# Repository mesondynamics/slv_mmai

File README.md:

# Mobile Machine Actuation Interface

**English** · [简体中文](README.zh-CN.md)

A hardware/software interface for retrofitting remote or autonomous control onto
electromechanical and electrohydraulic mobile machines.

MMAI connects an upper-level controller to the steering, propulsion, auxiliaries,
and available state feedback of an existing machine. This repository presents
the engineering approach through schematics, firmware, interface code, and its
development history. Read the source as working design material: it records the
hardware, communication, and actuation choices behind the ECU.

## What it does

- Receives commands from teleoperation or autonomy software.
- Validates commands and manages control authority, timeouts, and output enable.
- Maps commands to electrical interfaces such as relays, CAN-controlled actuators,
  or PWM-driven hydraulic valve coils.
- Acquires machine and actuator state and sends feedback to the upper layer.
- Keeps low-level machine behavior understandable independently of a planner.

The same architecture can be adapted to street sweepers, compactors, agricultural
machines, utility vehicles, and other mobile equipment. The appropriate actuator,
wiring, feedback, and stop behavior depend on the machine. Analog command outputs
or additional serial interfaces are adaptation options, not capabilities implied
for every board in this repository.

## Architecture

The machine-interface ECU sits between the command source and the physical
machine. Steering, propulsion, and auxiliary I/O are separate adaptation paths;
state feedback closes the path through the ECU. Existing manual controls and
machine interlocks are part of that integration.

Upper-level navigation, perception, and route planning are outside the core
actuation boundary. The retained implementation focuses on low-level actuation
and state feedback. See [Architecture](docs/architecture.md)
and [Interfaces](docs/interfaces.md).

## Implementation map

| Area | Start here | What to look for |
| --- | --- | --- |
| H563 actuation ECU | [Hardware project](pcb/roller/ecu/PROJECT1.kicad_pro), [firmware](firmware/roller/ECU/) | Relay switching, proportional-valve current control, CAN steering, protected control boundary |
| Mechanical material | [CAD](cad/), [PCB sources](pcb/) | Physical integration and board development |

Historical directory names are retained so code, drawings, and commits remain
easy to trace. They do not define the scope of the general architecture.

## A useful reading order

1. Read the [hardware guide](docs/hardware.md) and open the corresponding schematic.
2. Follow a command through the [firmware guide](docs/firmware.md): parser, control
   policy, machine mapping, then physical driver.
3. Follow feedback in the opposite direction, checking units and validity flags.
4. Compare earlier revisions using the [project history](docs/PROVENANCE.md).
5. Use the [porting guide](docs/porting-guide.md) to describe a different machine.

The H563 example includes an Ethernet command/state protocol, CAN interfaces,
relay/contact outputs, PWM valve drivers with current sensing, and analog,
discrete, and pulse inputs. Its wire protocol and I/O assignments are concrete
implementation choices; they are not a universal machine API.

## Safety and bench exploration

This is experimental engineering material, not a certified functional-safety
controller or a ready-to-install vehicle conversion. Physical deployment needs
machine-specific engineering. Begin any electrical exploration with isolated
signals and dummy loads, and understand startup, command-loss, manual-control,
and emergency-stop behavior before connecting actuators. See [Safety](docs/SAFETY.md).

## History and related work

The repository lineage begins in 2024. The public source centers on the
machine-interface ECU hardware and firmware, with retained design revisions
and technical notes. [Provenance](docs/PROVENANCE.md) identifies source milestones.

Electronic and electrohydraulic machine actuation has a long public engineering
history. [Prior art and related systems](docs/PRIOR_ART.md) provides technical
references for understanding these established approaches.

## License and contributions

Original project contributions use [BSD-2-Clause](LICENSE), subject to existing
file-specific notices. Bundled third-party material retains its own terms and
attribution; see the [license index](LICENSES/README.md).

Corrections, explanations, and clearly attributed design contributions are welcome.
See [Contributing](CONTRIBUTING.md) and [Security](SECURITY.md).

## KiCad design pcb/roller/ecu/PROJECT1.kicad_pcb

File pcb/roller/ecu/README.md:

# Actuation interface ECU hardware

**English** · [中文设计说明与完整参考资料](README.zh-CN.md)

This STM32H563-based board illustrates the electrical boundary between an
upper-level controller and existing machine actuators and sensors. Open
[PROJECT1.kicad_pro](PROJECT1.kicad_pro) and the
[root schematic](PROJECT1.kicad_sch) to explore the design.

The [hardware reading guide](../../../docs/hardware.md) maps the nine schematic
sheets to their functions. The [architecture](../../../docs/architecture.md)
places the board in the larger steering, propulsion, and auxiliary-I/O system.

## Design paths

- **Steering:** connect to a supported external actuator/controller; mechanical
  coupling and feedback depend on the machine.
- **Propulsion:** the reference circuit drives two proportional-valve coils with
  PWM and current sensing. The machine's hydraulic circuit determines how coil
  current affects propulsion.
- **Auxiliaries:** a serial driver chain and relay contacts can switch or select
  existing machine signals. Wiring and contact assignments remain machine-specific.
- **Feedback:** analog, temperature, isolated digital, pulse, and bus interfaces
  provide the inputs available to the selected integration.

## Circuit-source notes

The original [Chinese technical notes](README.zh-CN.md) include the detailed
PAGE1-PAGE9 circuit mapping, public source identifiers S01-S60, and illustrated
retrofit examples. Selected entry points are:

| Topic | Detailed notes |
| --- | --- |
| Steering actuators | [Motor/steering integration](README.zh-CN.md#steer-sys-01) |
| Proportional-valve drive | [PWM and current-sensing path](README.zh-CN.md#sol-os-01) |
| Relay/contact switching | [Relay interface path](README.zh-CN.md#rly-sys-01) |
| Solenoid reference circuit | [Analog Devices CN0415](README.zh-CN.md#s38) |
| Earlier hydraulic retrofit example | [CASE CX160 project reference](README.zh-CN.md#s60) |

These references explain particular design functions; they do not make all
machine interfaces interchangeable. Consult the selected board revision and
[safety guidance](../../../docs/SAFETY.md) before any physical integration.

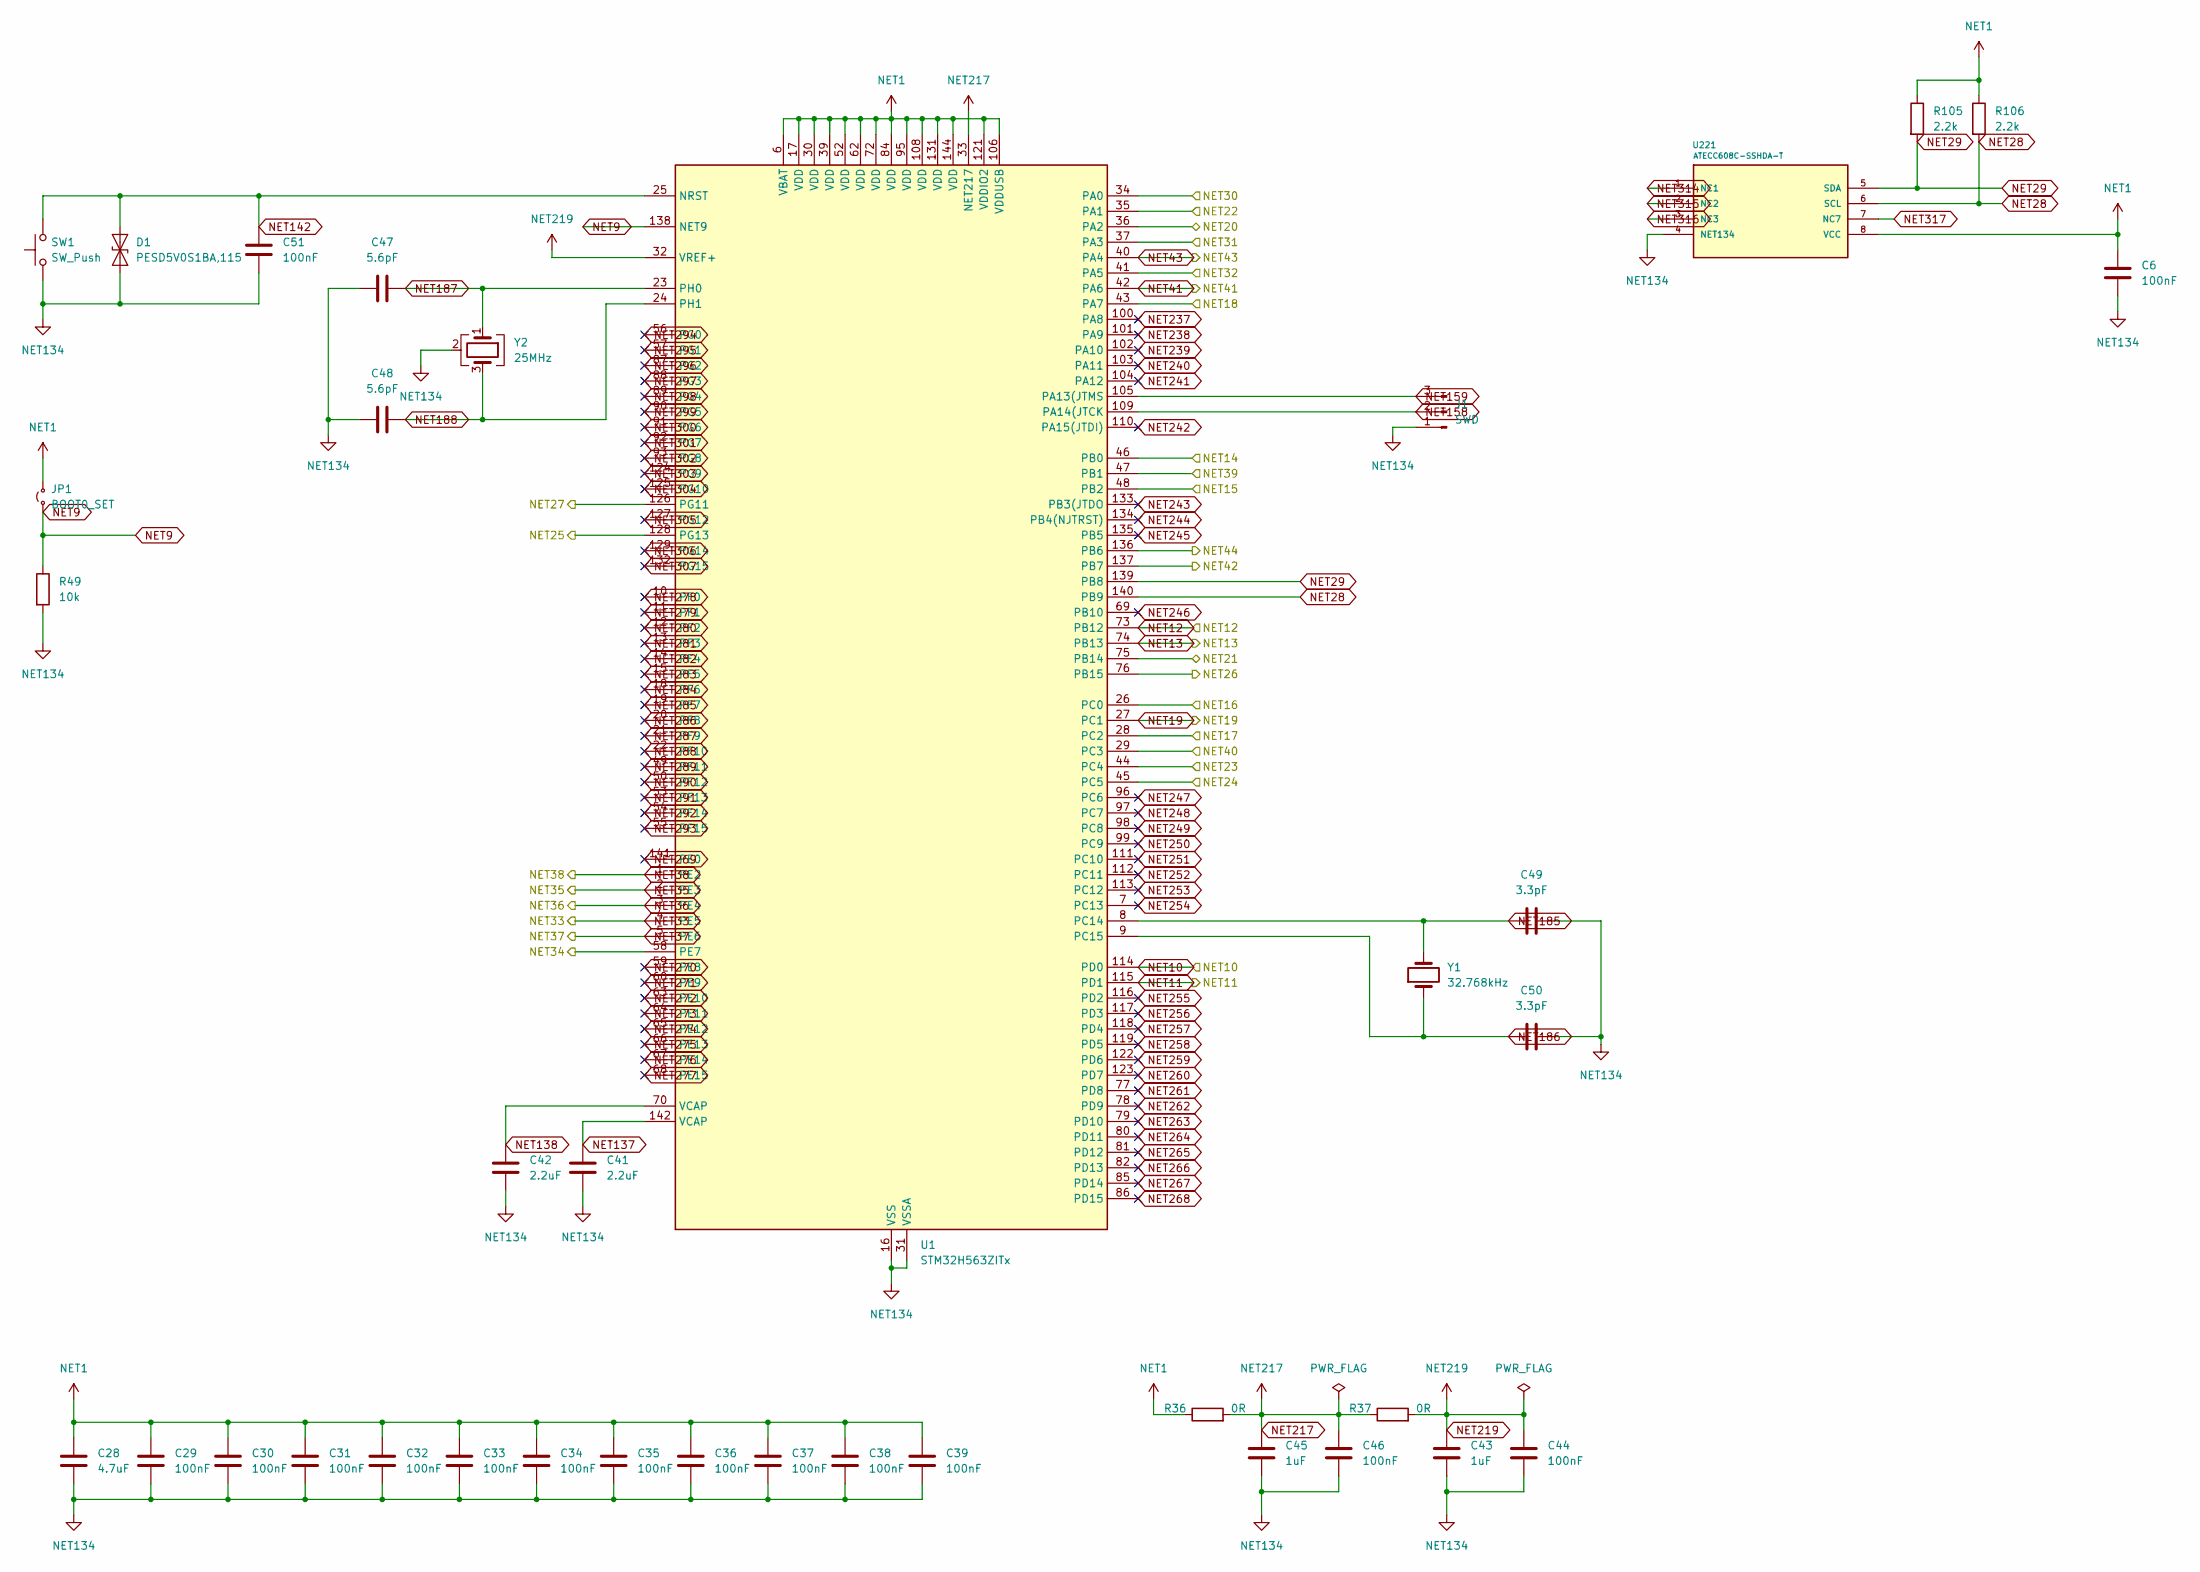
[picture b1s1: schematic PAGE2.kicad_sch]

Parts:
C6, C29, C30, C31, C32, C33, C34, C35, C36, C37, C38, C39, C44, C46, C51: 100nF; C_0603_1608Metric
C28: 4.7uF; C_0603_1608Metric
C41, C42: 2.2uF; C_0603_1608Metric
C43, C45: 1uF; C_0603_1608Metric
C47, C48: 5.6pF; C_0603_1608Metric
C49, C50: 3.3pF; C_0603_1608Metric
D1: PESD5V0S1BA,115; D_SOD-323
J1: SWD; PinHeader_1x03_P2.54mm_Vertical
JP1: BOOT0_SET; SolderJumper-2_P1.3mm_Open_TrianglePad1.0x1.5mm
R36, R37: 0R; R_0603_1608Metric
R49: 10k; R_0603_1608Metric
R105, R106: 2.2k; R_0603_1608Metric
SW1: SW_Push; SW_SPST_EVQPE1
U1: STM32H563ZITx; LQFP-144_20x20mm_P0.5mm
U221: ATECC608C-SSHDA-T; SOIC-8_3.9x4.9mm_P1.27mm
Y1: 32.768kHz; Crystal_SMD_3215-2Pin_3.2x1.5mm
Y2: 25MHz; Crystal_SMD_3225-4Pin_3.2x2.5mm

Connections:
NET1: C6.1, C28.1, C29.1, C30.1, C31.1, C32.1, C33.1, C34.1, C35.1, C36.1, C37.1, C38.1, C39.1, JP1.2 (B), R36.1, R105.1, R106.1, U1.6 (VBAT), U1.17 (VDD), U1.30 (VDD), U1.39 (VDD), U1.52 (VDD), U1.62 (VDD), U1.72 (VDD), U1.84 (VDD), U1.95 (VDD), U1.106 (VDDUSB), U1.108 (VDD), U1.121 (VDDIO2), U1.131 (VDD), U1.144 (VDD), U221.8 (VCC); also elsewhere on the board
NET9: JP1.1 (A), R49.1, U1.138 (BOOT0)
NET10: U1.114 (PD0); also elsewhere on the board
NET11: U1.115 (PD1); also elsewhere on the board
NET12: U1.73 (PB12); also elsewhere on the board
NET13: U1.74 (PB13); also elsewhere on the board
NET14: U1.46 (PB0); also elsewhere on the board
NET15: U1.48 (PB2); also elsewhere on the board
NET16: U1.26 (PC0); also elsewhere on the board
NET17: U1.28 (PC2); also elsewhere on the board
NET18: U1.43 (PA7); also elsewhere on the board
NET19: U1.27 (PC1); also elsewhere on the board
NET20: U1.36 (PA2); also elsewhere on the board
NET21: U1.75 (PB14); also elsewhere on the board
NET22: U1.35 (PA1); also elsewhere on the board
NET23: U1.44 (PC4); also elsewhere on the board
NET24: U1.45 (PC5); also elsewhere on the board
NET25: U1.128 (PG13); also elsewhere on the board
NET26: U1.76 (PB15); also elsewhere on the board
NET27: U1.126 (PG11); also elsewhere on the board
NET28: R106.2, U1.140 (PB9), U221.6 (SCL)
NET29: R105.2, U1.139 (PB8), U221.5 (SDA)
NET30: U1.34 (PA0); also elsewhere on the board
NET31: U1.37 (PA3); also elsewhere on the board
NET32: U1.41 (PA5); also elsewhere on the board
NET33: U1.4 (PE5); also elsewhere on the board
NET34: U1.58 (PE7); also elsewhere on the board
NET35: U1.2 (PE3); also elsewhere on the board
NET36: U1.3 (PE4); also elsewhere on the board
NET37: U1.5 (PE6); also elsewhere on the board
NET38: U1.1 (PE2); also elsewhere on the board
NET39: U1.47 (PB1); also elsewhere on the board
NET40: U1.29 (PC3); also elsewhere on the board
NET41: U1.42 (PA6); also elsewhere on the board
NET42: U1.137 (PB7); also elsewhere on the board
NET43: U1.40 (PA4); also elsewhere on the board
NET44: U1.136 (PB6); also elsewhere on the board
NET134: C6.2, C28.2, C29.2, C30.2, C31.2, C32.2, C33.2, C34.2, C35.2, C36.2, C37.2, C38.2, C39.2, C41.2, C42.2, C43.2, C44.2, C45.2, C46.2, C47.1, C48.1, C49.2, C50.2, C51.2, D1.1 (A1), J1.1, R49.2, SW1.1, U1.16 (VSS), U1.31 (VSSA), U1.38 (VSS), U1.51 (VSS), U1.61 (VSS), U1.71 (VSS), U1.83 (VSS), U1.94 (VSS), U1.107 (VSS), U1.120 (VSS), U1.130 (VSS), U1.143 (VSS), U221.4 (GND), Y2.2 (G), Y2.4 (G); also elsewhere on the board
NET137: C41.1, U1.142 (VCAP)
NET138: C42.1, U1.70 (VCAP)
NET142: C51.1, D1.2 (A2), SW1.2, U1.25 (NRST)
NET158: J1.2, U1.109 (PA14(JTCK)
NET159: J1.3, U1.105 (PA13(JTMS)
NET185: C49.1, U1.8 (PC14), Y1.2
NET186: C50.1, U1.9 (PC15), Y1.1
NET187: C47.2, U1.23 (PH0), Y2.1
NET188: C48.2, U1.24 (PH1), Y2.3
NET217: C45.1, C46.1, R36.2, R37.1, U1.33 (VDDA)
NET219: C43.1, C44.1, R37.2, U1.32 (VREF+)
NET237: U1.100 (PA8)
NET238: U1.101 (PA9)
NET239: U1.102 (PA10)
NET240: U1.103 (PA11)
NET241: U1.104 (PA12)
NET242: U1.110 (PA15(JTDI))
NET243: U1.133 (PB3(JTDO)
NET244: U1.134 (PB4(NJTRST))
NET245: U1.135 (PB5)
NET246: U1.69 (PB10)
NET247: U1.96 (PC6)
NET248: U1.97 (PC7)
NET249: U1.98 (PC8)
NET250: U1.99 (PC9)
NET251: U1.111 (PC10)
NET252: U1.112 (PC11)
NET253: U1.113 (PC12)
NET254: U1.7 (PC13)
NET255: U1.116 (PD2)
NET256: U1.117 (PD3)
NET257: U1.118 (PD4)
NET258: U1.119 (PD5)
NET259: U1.122 (PD6)
NET260: U1.123 (PD7)
NET261: U1.77 (PD8)
NET262: U1.78 (PD9)
NET263: U1.79 (PD10)
NET264: U1.80 (PD11)
NET265: U1.81 (PD12)
NET266: U1.82 (PD13)
NET267: U1.85 (PD14)
NET268: U1.86 (PD15)
NET269: U1.141 (PE0)
NET270: U1.59 (PE8)
NET271: U1.60 (PE9)
NET272: U1.63 (PE10)
NET273: U1.64 (PE11)
NET274: U1.65 (PE12)
NET275: U1.66 (PE13)
NET276: U1.67 (PE14)
NET277: U1.68 (PE15)
NET278: U1.10 (PF0)
NET279: U1.11 (PF1)
NET280: U1.12 (PF2)
NET281: U1.13 (PF3)
NET282: U1.14 (PF4)
NET283: U1.15 (PF5)
NET284: U1.18 (PF6)
NET285: U1.19 (PF7)
NET286: U1.20 (PF8)
NET287: U1.21 (PF9)
NET288: U1.22 (PF10)
NET289: U1.49 (PF11)
NET290: U1.50 (PF12)
NET291: U1.53 (PF13)
NET292: U1.54 (PF14)
NET293: U1.55 (PF15)
NET294: U1.56 (PG0)
NET295: U1.57 (PG1)
NET296: U1.87 (PG2)
NET297: U1.88 (PG3)
NET298: U1.89 (PG4)
NET299: U1.90 (PG5)
NET300: U1.91 (PG6)
NET301: U1.92 (PG7)
NET302: U1.93 (PG8)
NET303: U1.124 (PG9)
NET304: U1.125 (PG10)
NET305: U1.127 (PG12)
NET306: U1.129 (PG14)
NET307: U1.132 (PG15)
NET314: U221.1 (NC1)
NET315: U221.2 (NC2)
NET316: U221.3 (NC3)
NET317: U221.7 (NC7)

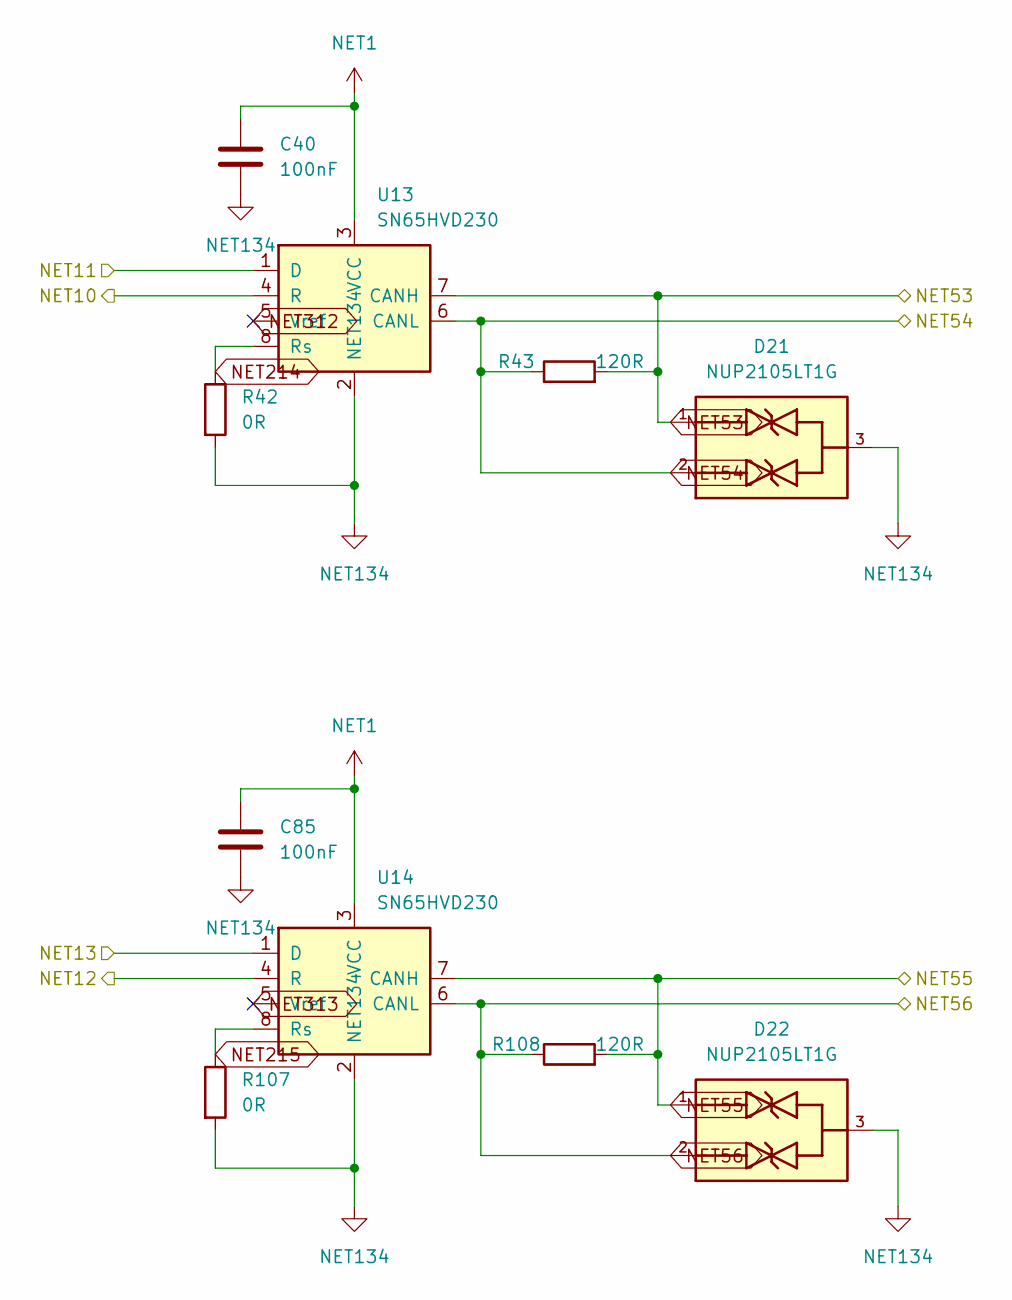
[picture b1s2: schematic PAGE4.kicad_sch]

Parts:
C40, C85: 100nF; C_0603_1608Metric
D21, D22: NUP2105LT1G; SOT95P237X111-3N; PARTREV 10
R42, R107: 0R; R_0603_1608Metric
R43, R108: 120R; R_0603_1608Metric
U13, U14: SN65HVD230; SOIC-8_3.9x4.9mm_P1.27mm

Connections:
NET1: C40.1, C85.1, U13.3 (VCC), U14.3 (VCC); also elsewhere on the board
NET10: U13.4 (R); also elsewhere on the board
NET11: U13.1 (D); also elsewhere on the board
NET12: U14.4 (R); also elsewhere on the board
NET13: U14.1 (D); also elsewhere on the board
NET53: D21.1, R43.2, U13.7 (CANH); also elsewhere on the board
NET54: D21.2, R43.1, U13.6 (CANL); also elsewhere on the board
NET55: D22.1, R108.2, U14.7 (CANH); also elsewhere on the board
NET56: D22.2, R108.1, U14.6 (CANL); also elsewhere on the board
NET134: C40.2, C85.2, D21.3, D22.3, R42.2, R107.2, U13.2 (GND), U14.2 (GND); also elsewhere on the board
NET214: R42.1, U13.8 (Rs)
NET215: R107.1, U14.8 (Rs)
NET312: U13.5 (Vref)
NET313: U14.5 (Vref)

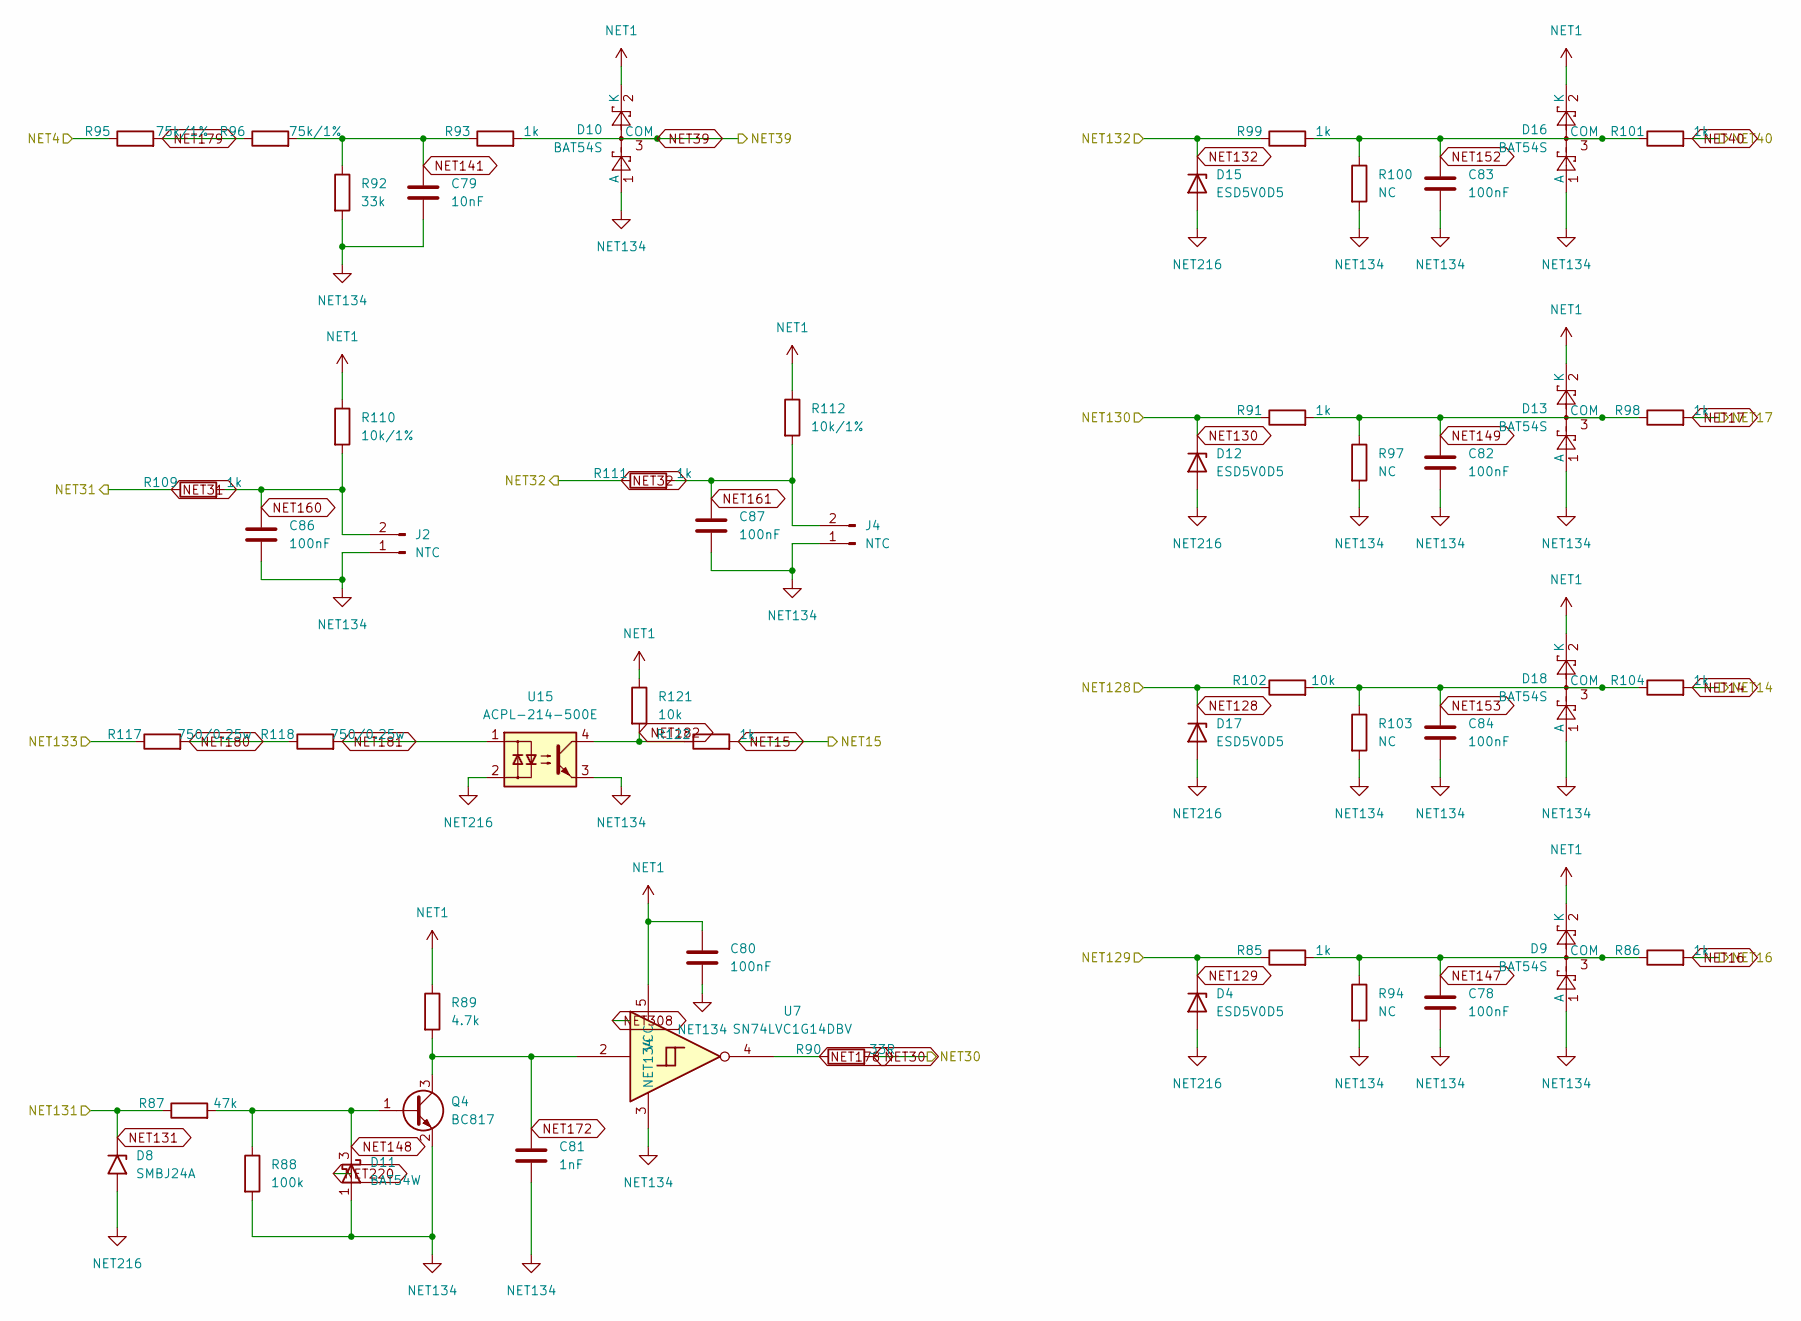
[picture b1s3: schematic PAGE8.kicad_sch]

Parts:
C78, C80, C82, C83, C84, C86, C87: 100nF; C_0603_1608Metric
C79: 10nF; C_0603_1608Metric
C81: 1nF; C_0603_1608Metric
D4, D12, D15, D17: ESD5V0D5; D_SOD-523
D8: SMBJ24A; D_SMB
D9, D10, D13, D16, D18: BAT54S; SOT-23
D11: BAT54W; SOT-323_SC-70
J2, J4: NTC; PinHeader_1x02_P2.54mm_Vertical
Q4: BC817; SOT-23
R85, R86, R91, R93, R98, R99, R101, R104, R109, R111, R122: 1k; R_0603_1608Metric
R87: 47k; R_0603_1608Metric
R88: 100k; R_0603_1608Metric
R89: 4.7k; R_0603_1608Metric
R90: 33R; R_0603_1608Metric
R92: 33k; R_0603_1608Metric
R94, R97, R100, R103: NC; R_0603_1608Metric
R95, R96: 75k/1%; R_0603_1608Metric
R102, R121: 10k; R_0603_1608Metric
R110, R112: 10k/1%; R_0603_1608Metric
R117, R118: 750/0.25w; R_1206_3216Metric
U7: SN74LVC1G14DBV; SOT-23-5
U15: ACPL-214-500E; SOP-4_4.4x2.6mm_P1.27mm

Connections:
NET1: C80.1, D9.2 (K), D10.2 (K), D13.2 (K), D16.2 (K), D18.2 (K), R89.1, R110.1, R112.1, R121.1, U7.5 (VCC); also elsewhere on the board
NET4: R95.1; also elsewhere on the board
NET14: R104.2; also elsewhere on the board
NET15: R122.2; also elsewhere on the board
NET16: R86.2; also elsewhere on the board
NET17: R98.2; also elsewhere on the board
NET30: R90.2; also elsewhere on the board
NET31: R109.1; also elsewhere on the board
NET32: R111.1; also elsewhere on the board
NET39: D10.3 (COM), R93.2; also elsewhere on the board
NET40: R101.2; also elsewhere on the board
NET128: D17.1 (K), R102.1; also elsewhere on the board
NET129: D4.1 (K), R85.1; also elsewhere on the board
NET130: D12.1 (K), R91.1; also elsewhere on the board
NET131: D8.1 (A1), R87.1; also elsewhere on the board
NET132: D15.1 (K), R99.1; also elsewhere on the board
NET133: R117.1; also elsewhere on the board
NET134: C78.2, C79.2, C80.2, C81.2, C82.2, C83.2, C84.2, C86.2, C87.2, D9.1 (A), D10.1 (A), D11.1 (A), D13.1 (A), D16.1 (A), D18.1 (A), J2.1, J4.1, Q4.2 (E), R88.2, R92.2, R94.2, R97.2, R100.2, R103.2, U7.3 (GND), U15.3; also elsewhere on the board
NET141: C79.1, R92.1, R93.1, R96.2
NET147: C78.1, D9.3 (COM), R85.2, R86.1, R94.1
NET148: D11.3 (K), Q4.1 (B), R87.2, R88.1
NET149: C82.1, D13.3 (COM), R91.2, R97.1, R98.1
NET152: C83.1, D16.3 (COM), R99.2, R100.1, R101.1
NET153: C84.1, D18.3 (COM), R102.2, R103.1, R104.1
NET160: C86.1, J2.2, R109.2, R110.2
NET161: C87.1, J4.2, R111.2, R112.2
NET172: C81.1, Q4.3 (C), R89.2, U7.2
NET178: R90.1, U7.4
NET179: R95.2, R96.1
NET180: R117.2, R118.1
NET181: R118.2, U15.1
NET182: R121.2, R122.1, U15.4
NET216: D4.2 (A), D8.2 (A2), D12.2 (A), D15.2 (A), D17.2 (A), U15.2; also elsewhere on the board
NET220: D11.2 (NC)
NET308: U7.1 (NC)

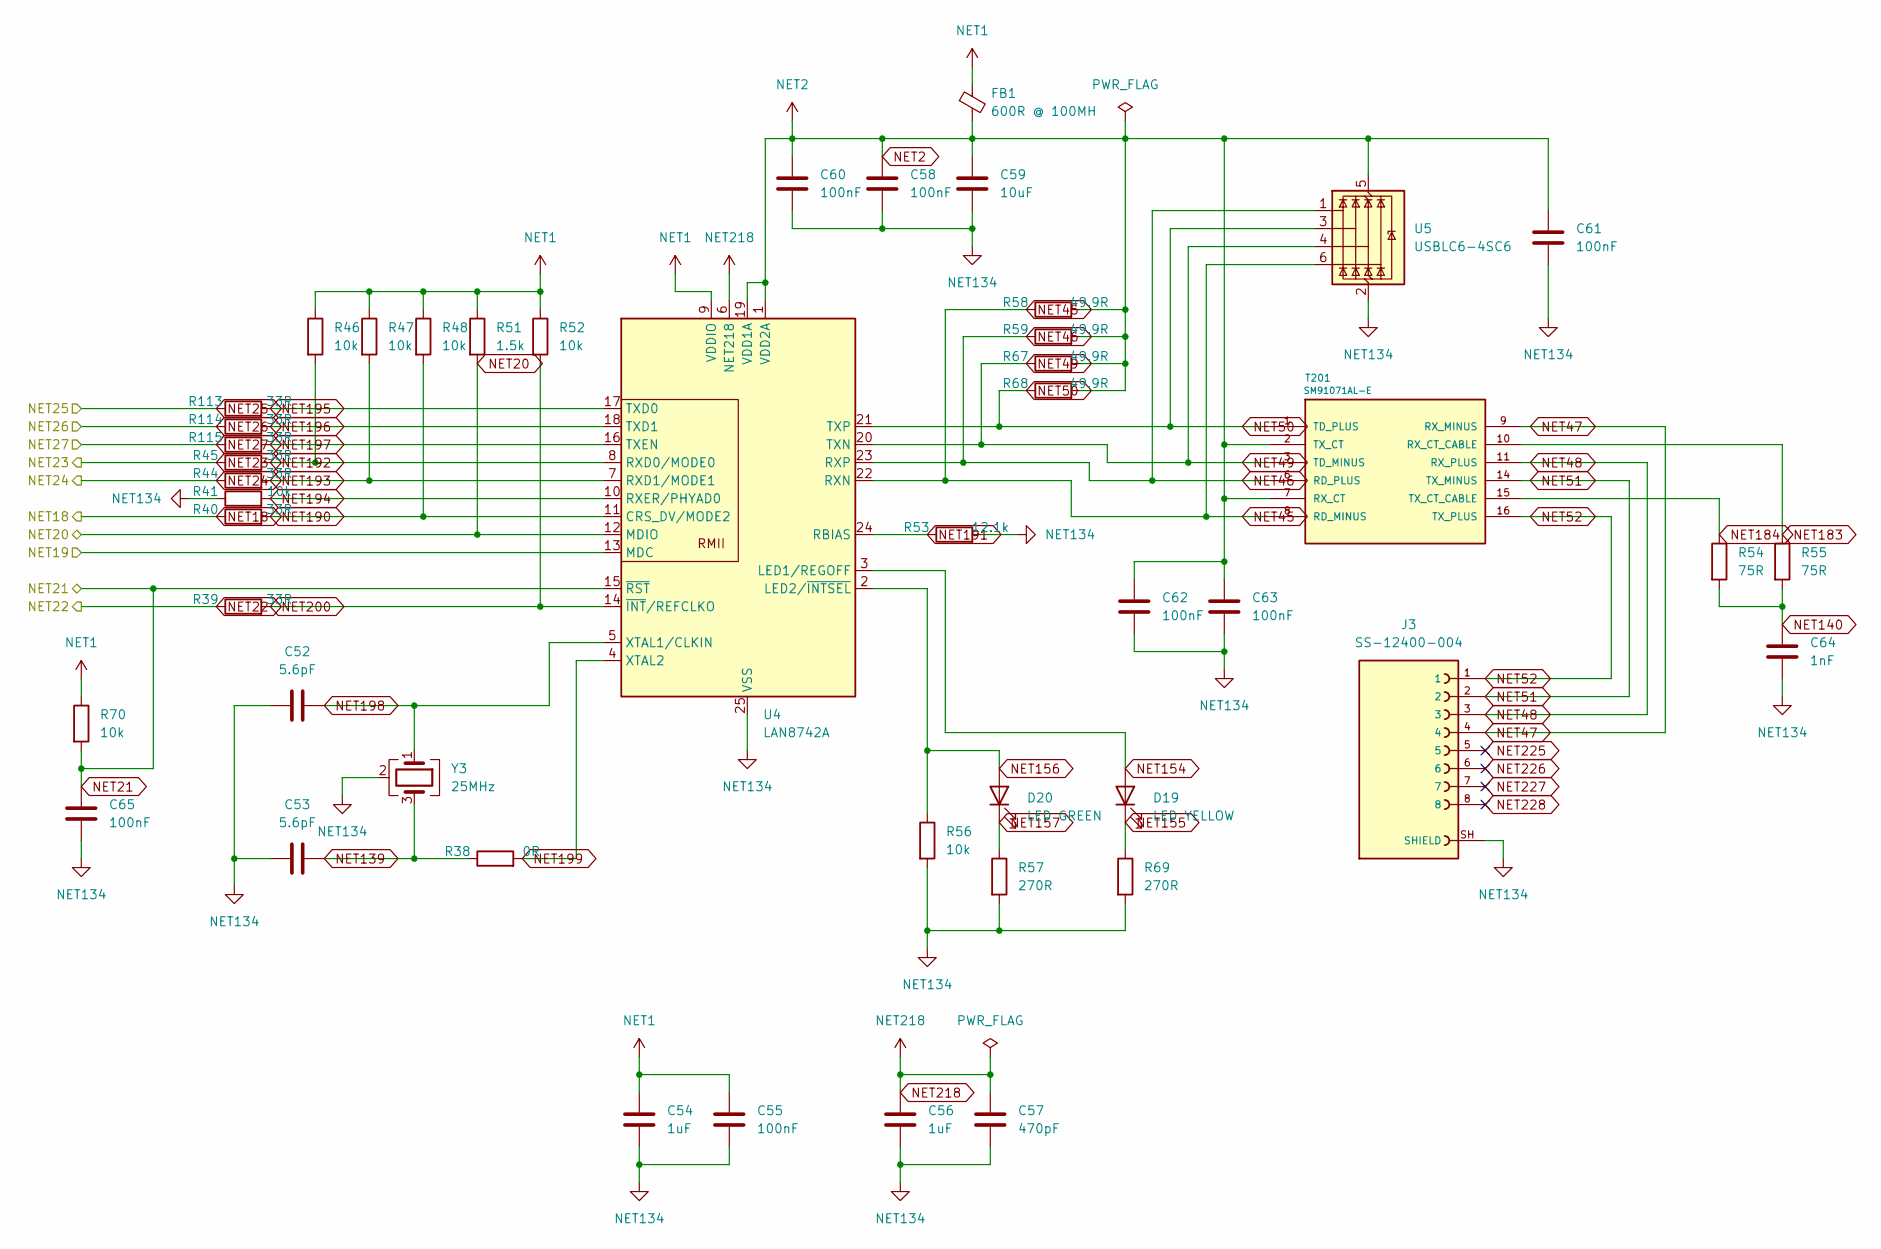
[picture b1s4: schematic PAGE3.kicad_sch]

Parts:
C52, C53: 5.6pF; C_0603_1608Metric
C54, C56: 1uF; C_0603_1608Metric
C55, C58, C60, C61, C62, C63, C65: 100nF; C_0603_1608Metric
C57: 470pF; C_0603_1608Metric
C59: 10uF; C_0603_1608Metric
C64: 1nF; C_0603_1608Metric
D19: LED YELLOW; LED_0603_1608Metric
D20: LED GREEN; LED_0603_1608Metric
FB1: 600R @ 100MH; L_0805_2012Metric
J3: SS-12400-004; CINCH_SS-12400-004; PARTREV A0
R38: 0R; R_0603_1608Metric
R39, R40, R44, R45, R113, R114, R115: 33R; R_0603_1608Metric
R41, R46, R47, R48, R52, R56, R70: 10k; R_0603_1608Metric
R51: 1.5k; R_0603_1608Metric
R53: 12.1k; R_0603_1608Metric
R54, R55: 75R; R_0603_1608Metric
R57, R69: 270R; R_0603_1608Metric
R58, R59, R67, R68: 49.9R; R_0603_1608Metric
T201: SM91071AL-E; Bourns_SM91071AL-E
U4: LAN8742A; VQFN-24-1EP_4x4mm_P0.5mm_EP2.5x2.5mm_POFV
U5: USBLC6-4SC6; SOT-23-6
Y3: 25MHz; Crystal_SMD_3225-4Pin_3.2x2.5mm

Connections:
NET1: C54.1, C55.1, FB1.1, R46.1, R47.1, R48.1, R51.1, R52.1, R70.1, U4.9 (VDDIO); also elsewhere on the board
NET2: C58.1, C59.1, C60.1, C61.1, C62.1, C63.1, FB1.2, R58.2, R59.2, R67.2, R68.2, T201.2 (TX_CT), T201.7 (RX_CT), U4.1 (VDD2A), U4.19 (VDD1A), U5.5 (VBUS)
NET18: R40.1; also elsewhere on the board
NET19: U4.13 (MDC); also elsewhere on the board
NET20: R51.2, U4.12 (MDIO); also elsewhere on the board
NET21: C65.1, R70.2, U4.15 (~RST); also elsewhere on the board
NET22: R39.1; also elsewhere on the board
NET23: R45.1; also elsewhere on the board
NET24: R44.1; also elsewhere on the board
NET25: R113.1; also elsewhere on the board
NET26: R114.1; also elsewhere on the board
NET27: R115.1; also elsewhere on the board
NET45: R58.1, T201.8 (RD_MINUS), U4.22 (RXN), U5.6 (I/O4)
NET46: R59.1, T201.6 (RD_PLUS), U4.23 (RXP), U5.1 (I/O1)
NET47: J3.4, T201.9 (RX_MINUS)
NET48: J3.3, T201.11 (RX_PLUS)
NET49: R67.1, T201.3 (TD_MINUS), U4.20 (TXN), U5.4 (I/O3)
NET50: R68.1, T201.1 (TD_PLUS), U4.21 (TXP), U5.3 (I/O2)
NET51: J3.2, T201.14 (TX_MINUS)
NET52: J3.1, T201.16 (TX_PLUS)
NET134: C52.1, C53.1, C54.2, C55.2, C56.2, C57.2, C58.2, C59.2, C60.2, C61.2, C62.2, C63.2, C64.2, C65.2, J3.SH (SHIELD), R41.1, R53.2, R56.2, R57.2, R69.2, U4.25 (VSS), U5.2 (GND), Y3.2 (G), Y3.4 (G); also elsewhere on the board
NET139: C53.2, R38.1, Y3.3
NET140: C64.1, R54.2, R55.2
NET154: D19.2 (A), U4.3 (LED1/REGOFF)
NET155: D19.1 (K), R69.1
NET156: D20.2 (A), R56.1, U4.2 (LED2/~INTSEL)
NET157: D20.1 (K), R57.1
NET183: R55.1, T201.10 (RX_CT_CABLE)
NET184: R54.1, T201.15 (TX_CT_CABLE)
NET190: R40.2, R48.2, U4.11 (CRS_DV/MODE2)
NET191: R53.1, U4.24 (RBIAS)
NET192: R45.2, R46.2, U4.8 (RXD0/MODE0)
NET193: R44.2, R47.2, U4.7 (RXD1/MODE1)
NET194: R41.2, U4.10 (RXER/PHYAD0)
NET195: R113.2, U4.17 (TXD0)
NET196: R114.2, U4.18 (TXD1)
NET197: R115.2, U4.16 (TXEN)
NET198: C52.2, U4.5 (XTAL1/CLKIN), Y3.1
NET199: R38.2, U4.4 (XTAL2)
NET200: R39.2, R52.2, U4.14 (~INT/REFCLKO)
NET218: C56.1, C57.1, U4.6 (VDDCR)
NET225: J3.5
NET226: J3.6
NET227: J3.7
NET228: J3.8

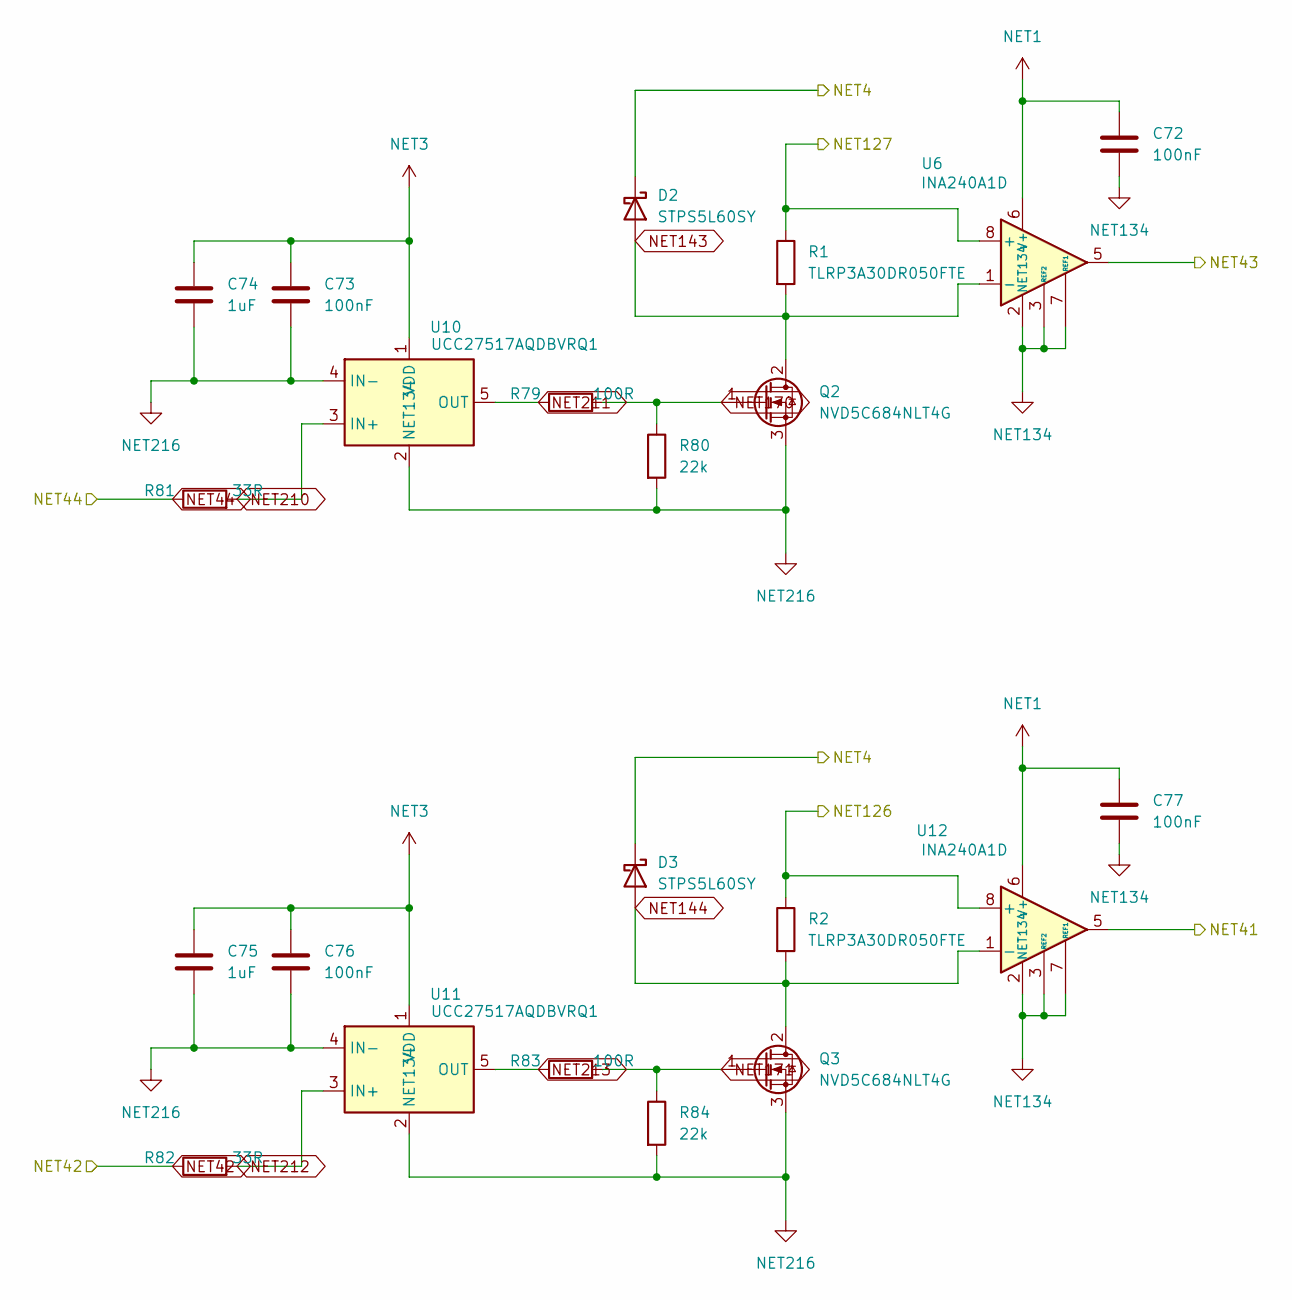
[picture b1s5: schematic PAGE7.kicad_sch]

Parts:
C72, C73, C76, C77: 100nF; C_0603_1608Metric
C74, C75: 1uF; C_0603_1608Metric
D2, D3: STPS5L60SY; D_SMC
Q2, Q3: NVD5C684NLT4G; TO-252-2
R1, R2: TLRP3A30DR050FTE; R_2512_6332Metric
R79, R83: 100R; R_0603_1608Metric
R80, R84: 22k; R_0603_1608Metric
R81, R82: 33R; R_0603_1608Metric
U6, U12: INA240A1D; SOIC-8_3.9x4.9mm_P1.27mm
U10, U11: UCC27517AQDBVRQ1; SOT-23-5_TI_DBV

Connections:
NET1: C72.1, C77.1, U6.6 (V+), U12.6 (V+); also elsewhere on the board
NET3: C73.1, C74.1, C75.1, C76.1, U10.1 (VDD), U11.1 (VDD); also elsewhere on the board
NET4: D2.1 (K), D3.1 (K); also elsewhere on the board
NET41: U12.5; also elsewhere on the board
NET42: R82.1; also elsewhere on the board
NET43: U6.5; also elsewhere on the board
NET44: R81.1; also elsewhere on the board
NET126: R2.1, U12.8 (+); also elsewhere on the board
NET127: R1.1, U6.8 (+); also elsewhere on the board
NET134: C72.2, C77.2, U6.2 (GND), U6.3 (REF2), U6.4 (GND), U6.7 (REF1), U12.2 (GND), U12.3 (REF2), U12.4 (GND), U12.7 (REF1); also elsewhere on the board
NET143: D2.2 (A), Q2.2 (D), R1.2, U6.1 (-)
NET144: D3.2 (A), Q3.2 (D), R2.2, U12.1 (-)
NET170: Q2.1 (G), R79.2, R80.1
NET171: Q3.1 (G), R83.2, R84.1
NET210: R81.2, U10.3 (IN+)
NET211: R79.1, U10.5 (OUT)
NET212: R82.2, U11.3 (IN+)
NET213: R83.1, U11.5 (OUT)
NET216: C73.2, C74.2, C75.2, C76.2, Q2.3 (S), Q3.3 (S), R80.2, R84.2, U10.2 (GND), U10.4 (IN-), U11.2 (GND), U11.4 (IN-); also elsewhere on the board
